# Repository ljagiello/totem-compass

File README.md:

# Totem Compass firmware — reverse engineering

Independent, unofficial reverse-engineering notes for the **Totem Compass** ESP32
firmware (**v5.0.3**; v5.0.2 was analyzed first, see
[What changed in 5.0.3](docs/firmware/changes-5.0.3.mdx)), produced by static analysis of the
publicly downloadable firmware images and the companion mobile app, plus a BLE client tested
against the author's own device. Not affiliated with or endorsed by Totem Labs.

## Key findings

- The device is an **ESP32** (Xtensa LX6) running **MicroPython v1.25.0** on **ESP-IDF v5.4**.
- Totem's application is **Python**, frozen into the image as bytecode across **94 frozen modules** in v5.0.3 (96 in v5.0.2), plus 2 non-frozen on-flash `.py` files.
- Three radios share the 2.4 GHz band: **BLE** (phone app), **ESP-NOW** ("Unity Mesh",
  Totem-to-Totem), and **WiFi** (station-mode OTA; the hotspot path is sunset).
- Application messages use a shared `(cat_id, cmd_id)` model with a common chunking layer.

## Documentation

Full docs live in [`docs/`](docs/) as a [Mintlify](https://mintlify.com) site.

```bash
cd docs
npm i -g mint    # or: npx mint@latest
mint dev         # preview at http://localhost:3000
```

Start at [`docs/index.mdx`](docs/index.mdx). The 2.4 GHz protocol capture — with a
completeness matrix — is under [`docs/protocols/`](docs/protocols/).

## Go client: `totemctl`

A Bluetooth LE client that speaks the same protocol as the official app: the
ConnStatus-Ready handshake, Live/Static/Peer records, and the half-duplex TX
handoff. No pairing or keys are needed.

```bash
go install github.com/ljagiello/totem-compass/cmd/totemctl@latest

totemctl scan                     # find Totems (double-press the power button first)
totemctl info                     # name, firmware, battery, position, settings
totemctl watch                    # stream live data and peer updates
totemctl peers                    # bonded Totems and points of interest
totemctl name "Base Camp"         # rename
totemctl compass --lock on --north off --blink on
totemctl power eco --blink on     # or: normal
totemctl wifi scan                # networks the Totem can see
totemctl wifi set <ssid>          # network used for firmware updates; asks for the password
totemctl peer color <mac> hot_pink
totemctl poi add --name "Main Stage" --lat 50.0671 --lon 19.9124 --sticky
totemctl location --lat 50.0671 --lon 19.9124  # feed a phone-style GNSS fix + clock
```

Pick a device with `-d <address substring>`, using an address `totemctl scan`
prints: every Totem advertises as "totem", so the name set with `totemctl name`
cannot select one. Get machine-readable output with `--json`, and log every
frame with `--trace`. `totemctl help <command>` lists each command's flags.

Every global flag can also be set as a `TOTEM_<FLAG>` environment variable
(`TOTEM_DEVICE`, `TOTEM_HALF_DUPLEX`, …) or in a config file with the long flag
names as keys (`device: <address from totemctl scan>`). The default location is
`totemctl/config.yaml` under the user config directory (`~/Library/Application
Support` on macOS, `~/.config` on Linux), or pass `--config`.

`compass` and `power` send a frame that always sets peer blink, which the Totem
does not report, so they need `--blink on|off`; set it once with `blink: on` in
the config file or `TOTEM_BLINK`.

The Ready frame's schema id selects one of two device transmit loops. The
client defaults to the legacy full-duplex loop (schema 0: notifications plus
app-level acks), which works on every platform. The newer half-duplex loop
(`--half-duplex`) sends indications and drops a record unless it is confirmed
within 500 ms; CoreBluetooth subscribes these characteristics for
notifications only, so that mode stalls on macOS.

Verified on hardware from macOS: `scan` and `info` on firmware 4.1.3 and 5.0.3; `watch` and
`compass --lock on|off` round-trips on 4.1.3. The other commands are built from the
v5.0.2/v5.0.3 bytecode (their handlers are identical in both) and covered by unit tests
only.

| Package | Contents |
| --- | --- |
| [`protocol/`](protocol/) | frame builders and decoders, no BLE dependency; tested against vectors built with the firmware's own `struct` formats |
| [`client/`](client/) | scanning, connecting, subscriptions, acks and TX-window handling on [`tinygo.org/x/bluetooth`](https://github.com/tinygo-org/bluetooth) (tested on macOS; the library also supports Linux/BlueZ and Windows) |
| [`cmd/totemctl/`](cmd/totemctl/) | the CLI |

## ESP32 emulator: `totememu`

An ESP32 running TinyGo that joins the ESP-NOW mesh as another Totem: it pairs with a real
Totem through the normal Touch Crystal pairing and then exchanges peer status with it every
radio window. It models the rest of the device too — the halo and the crystal, the Touch
Crystal and the two buttons, the power state and its battery curve, an update over WiFi —
and keeps its name, colour and bonds in flash across a power cut. Hardware-tested against
firmware 5.0.3. See [`docs/reference/esp32-emulator.mdx`](docs/reference/esp32-emulator.mdx).

```bash
tinygo flash -target esp32-generic -ldflags "-X main.owned=<your Totem's MAC>" ./cmd/totememu

totemctl mesh pair                # hold the Totem's Touch Crystal next to the board
totemctl mesh watch               # decode every frame the Totem sends it (--raw, --tx, --json)
totemctl mesh status              # the emulator and its peers
totemctl mesh clock               # give the board this computer's time
totemctl mesh send pos 50.0671 19.9124 3   # where it is
totemctl mesh send sim walk 90             # and where it goes: walk, drive or still
totemctl mesh send batt 40                 # also: sos, heading, flat, unbond, selftest
totemctl mesh send touch crystal hold 1500 # a gesture, as a finger would make it
totemctl mesh send leds                    # what the ring and the crystal are doing
```

The `mesh` commands find the board's USB serial port by itself (or take `--port`,
`TOTEM_PORT`, `port:` in the config file). They open it without toggling DTR/RTS, so the
board does not reboot, and they decode the raw frames on the host with the `mesh` package.

| Package | Contents |
| --- | --- |
| [`mesh/`](mesh/) | ESP-NOW frame codec (peer, locate, Smart Group), tested against frames packed with the firmware's own `struct` formats |
| [`emulator/`](emulator/) | the Totem logic: pairing, radio windows, clock sync, locate reply and relay, Smart Group member, the halo and crystal, the touch and button gestures, the power state and the WiFi update, and a model of the GNSS receiver, compass, motion sensor and battery; host-tested |
| [`store/`](store/) | the settings and bonds a reboot keeps, as an append-only journal in one flash sector |
| [`cmd/totememu/`](cmd/totememu/) | the ESP32 firmware and its serial console |

## Scope & ethics

The firmware analysis is static and no service was attacked; the releases API and firmware
objects are served publicly. The only code run against hardware is `totemctl`, over BLE, and
`totememu`, over ESP-NOW, both on the author's own Totem. See
[`docs/reference/methodology.mdx`](docs/reference/methodology.mdx). Use them only with devices
you own. The mesh and demi-god paths can affect other people's Totems nearby, so `totemctl`
does not send those commands, and `totememu` talks only to the Totems it is built for, never
hosts a Smart Group and never sends demi-god commands.

## License

Licensed under the [Apache License 2.0](LICENSE).

Created by [Lukasz Jagiello](https://lukasz.jagiello.org). Write-up: [lukasz.jagiello.org/projects/totem-compass](https://lukasz.jagiello.org/projects/totem-compass).

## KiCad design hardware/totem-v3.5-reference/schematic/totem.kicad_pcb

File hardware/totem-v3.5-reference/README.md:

# Totem v3.5 — reference design

A working circuit built from the parts identified on a Totem v3.5, with the
values chosen by calculation and checked in ngspice.

**This is a reconstruction, not a recovery.** The parts and the MCU pin
assignments are established — the parts off the board, the pins out of the
firmware, both cited in [the hardware page](../../docs/reference/hardware.mdx).
Everything else here is *designed to satisfy those facts*, not traced from the
PCB. Resistor values, the regulator topology, the LED supply arrangement: all
chosen here. Where a value is derived from something the firmware does, the
derivation is shown, and that is the strongest claim any of it makes.

Passive values cannot be recovered from photographs of an assembled board.
What can be done is to work out what they would have to be for the firmware to
behave as it does, and then check that circuit holds up. That is what this is.

## What the firmware pins down

Two constants in the firmware constrain the analog design tightly enough to
solve for it.

### The battery divider is determined, not chosen

The firmware converts its ADC reading with a fixed calibration
(`docs/subsystems/power.mdx`, `compass.dis:1446`):

```python
battery_volt = 0.0017 * self.v_supply.read() + 0.206
```

`ADC.read()` returns 0..4095. Writing the whole chain out, with `k` the
divider ratio, `VFS` the ATTN_11DB full scale and `Voff` the ADC's input
offset:

```
cal(V) = 0.0017 * 4095 * (k*V - Voff)/VFS + 0.206
```

For `cal(V) == V` at every V, both coefficients must match:

```
k    = VFS / (0.0017 * 4095) = 3.3 / 6.9615 = 0.4741
Voff = 0.206 * VFS / 6.9615  = 97.7 mV
```

The offset is not fitted — it falls out of the same two equations, and
**97.7 mV is the ESP32 ADC's well-known input offset**. That it lands there
is the evidence the model has the right shape, and it is why the `+0.206` in
the firmware is an ADC artefact rather than a fudge.

A resistor marked `124` — 120 kΩ — is on the board. Taking that as the top
leg, the ratio asks for 108.2 kΩ below it, and no standard series has that
(E96 goes 107, 110; E192 107, 109). An earlier version named a 108 kΩ
part, which is not made; the nearest that is, 109 kΩ, reads a full cell
17 mV high, over the 10 mV the checks allow. So this board uses
**113 kΩ over 102 kΩ**, both E96 and both made in 0.1%: k within 0.08% of
the firmware's, drawing 19.5 µA.
Simulated, the firmware's own calibration then reads the cell **true to
3.3 mV** across 3.4–4.2 V, against 68 mV for the 120k/100k pair tried first.

### GPIO 39 is a VBUS divider, not the charger's status pin

`modes.is_charging = self.v_in.value()` — high means charging. The TP4056's
`CHRG` is open-drain and pulls **low** while charging, and GPIO 34–39 have no
internal pull of any kind, so an open-drain source would float when idle.
Both facts are wrong for `CHRG` and right for a divider off VBUS, which also
matches the firmware's own name for it: `v_in`, the input voltage.

100 kΩ over 150 kΩ clears the logic threshold at a sagging 4.40 V charger and
stays under the absolute maximum at 5.25 V, with margin at both ends.

## Verification

```
cd sim && python3 check.py
```

Requires `ngspice` (`brew install ngspice`). Each deck computes; `check.py`
decides whether the number is allowed, and prints a line per claim. Current
state: **18 passed, 0 failed, 1 known limit recorded**.

| Block | Result |
| --- | --- |
| `batt_sense` | Pin at 1.993 V on a full cell, inside the ADC's 150–2450 mV window. Calibration true to 3.3 mV. Divider (113k over 102k) draws 19.5 µA |
| `vbus_sense` | 2.64 V at 4.40 V in (165 mV over V<sub>IH</sub>), 3.15 V at 5.25 V (450 mV under absolute max). 21 µA |
| `ldo_headroom` | Rail holds 3.293 V at a 3.4 V cell under a 532 mA peak — 293 mV over the ESP32's minimum. Fails only at 3.107 V, *below* the firmware's cutoff |
| `led_budget` | With the 1515's 15.5 mA per pixel: normal use is 0.15 C, all 67 pixels at full white at the firmware's brightness 0.62 C; 1 C would take 107. Known limit: the pixels want 3.5 V and the firmware runs the cell to 3.15 V |

The digital parts are modelled as current sinks at their datasheet peaks, and
the regulator and charger behaviourally, because no vendor models are to hand.
These verify the design's arithmetic, not anyone's silicon.

The whole board is simulated too, built from the schematic's own netlist
rather than from a hand-written deck:

```
cd sim && python3 board_sim.py
```

**78 passed, 0 failed, 1 known limit**, over five corners (cell at 4.2, 3.8
and 3.4 V; the 2N7002's threshold at 2.1 and 2.5 V). Each corner runs one
4.5-second sequence — off, press on, press while running, ring on and off,
firmware power-off, on again, held through a firmware power-off, released —
and checks the rail, GPIO 4's voltage limits and the cell's idle drain at each
step. Steady-state checks cover the rail at a TX peak with the ring lit across
the firmware's battery bands, every pixel at full white, both sense dividers
and charging. The known limit is the ring's supply at a 3.45 V cell, 3.34 V
against the 1515 LEDs' 3.5 V rating, which the reference board shares: its
ring hangs off the cell the same way.

## The board

`schematic/totem.kicad_pcb`, made by scripts in `pcb/` from the schematic
and from measurements of the reference board's photographs (`measure/`,
whose README says how, and how well, each number is known):

```
cd pcb
KP=/Applications/KiCad/KiCad.app/Contents/Frameworks/Python.framework/Versions/Current/bin/python3
$KP build.py      # outline, parts where the photos put them, nets, planes, rules
python route.py   # the router (numpy, scipy, opencv)
$KP apply.py      # tracks and vias into the board, zones filled
$KP models.py     # 3D models for the parts KiCad's library has none for
python3 fab.py    # everything for the fab and the assembler -> pcb/fab/
```

**To have boards made, hand over `pcb/fab/totem-v3.5-assembly-package.zip`.** It
holds gerbers and drills (and ODB++ and IPC-2581), the BOM and placement file,
assembly drawings, the schematic, a STEP model, and
[`pcb/ASSEMBLY.md`](pcb/ASSEMBLY.md): what to order, how to assemble, bring up
and program the board, and what to measure before ordering.

Four layers, 1.6 mm: signals on both outer layers, In1 solid GND, In2 3V3.
Tracks 0.13 mm and 0.13 mm apart, power nets 0.4 mm with 0.2 mm; vias
0.45/0.2 mm; copper 0.3 mm from the edge — a mainstream 4-layer process with
margin. The GNSS antenna feed is a straight, via-free 0.38 mm microstrip on
F.Cu over In1: 50 Ω on a standard 1.6 mm 4-layer stack-up (about 0.21 mm of
7628 prepreg under the top layer); order that stack-up, or re-size the line
for another. The LED side's ring is powered through a VLED pour outside the
ring, fed at C16 and, past the one place the ring's data has to cross it,
at D159.

Both sides carry parts (the LED side: ring, crystal, motion sensor and
magnetometer, microphone, the charge LEDs, the power latch), so assembly is
double-sided. The placement file is KiCad's;
assembly houses differ in how they read rotations on the bottom side, so
check their preview of the LED side — the ring's orientation rule is that
each LED's DI and VDD pads face out.

**`kicad-cli pcb drc --schematic-parity --severity-all`: 0 violations,
0 unconnected pads, 0 footprint errors.** Three places where the reference
board is closer than KiCad's courtyard and silkscreen margins allow (the
TP4056 0.3 mm from the module, the SOS LED between its switch's legs) are
narrow rules in `schematic/totem.kicad_dru`, each with its reason. The
router (`pcb/route.py`) also checks every net's connectivity itself before
it hands over.

What is the reference board's and what is not:

| | |
| --- | --- |
| Outline, notches, the tab | Measured: ±0.3 mm on the left half and bottom, **±1.3 mm in height on the right side** (the two photos disagree there) |
| ESP32, MAX-M10S, TP4056, LDO, u.FL, P-FET, switches, SOS LED | Measured from their pads |
| The ring | Measured: centre (−2.02, 2.45), radius 18.24 mm, 60 LEDs every 6°, **1.5 mm packages** |
| The crystal, its pogo-pin post, the IMU's site, the microphone | Measured |
| The two charge LEDs and their two resistors in the crystal, the JST's pins | Measured from close-ups of the LED side |
| The motion sensor and magnetometer | This design's: the reference board's ICM-20948 is obsolete, so an ST LSM6DSV16X sits on its site with an LIS2MDL beside it (below) |
| Passives, the latch, the ring's driver | This design's, placed beside what they serve |
| About 25 small parts in the reference board's LED-side cluster below the crystal, and a column of about 8 between the ring and the crystal | Photographed, not copied: their values and nets run under the parts and on inner layers. This design's own circuit does the jobs they must do (latch, ring switch, decoupling) |
| Every trace | Routed here; the original's are not recoverable |

**Measure these on the reference board before ordering** — each is where a
photograph could not settle it:

- **The board's height at the right edge**, and the distance from the USB-C
  to the lower-right notch: the right side is known to ±1.3 mm.
- **The USB-C.** The original's is a through-hole-shell part: on the LED
  side its four plated slots sit 4.80 mm either side of the centre line in
  two rows 3.0 mm apart, with two round holes 6.5 mm apart (measured,
  `measure/`). No catalogue footprint checked matches that (HRO
  TYPE-C-31-M-12, GCT USB4105 and USB4125, SHOU HAN TYPE-C 6P and its
  recessed 6P). The one used here, a power-only GCT USB4135, is the library
  part that clears the ring behind it; its plug face ends up **about 0.6 mm
  or more further in** than the original's (1.75 mm overhang). Check it
  against the case, and measure the original's if it can be taken out.
- **The JST** is the through-hole S2B-PH-K-S on the reference board's own
  pin positions (their solder joints, 1.96 mm apart, show on the LED side);
  its housing overhangs the lower-right chamfer as the original's does.
  Check the cable's exit against the case.
- **Button stem height.** The switches are 6 x 6 mm top-actuated tact
  switches with tall stems that go through the rear cover; the BOM names a
  9.5 mm one. The stem has to be matched to the cover.
- **The touch pogo pin**: a gold spring-loaded pin standing on the 2.5 mm
  pad at the centre of the crystal (close-up photo). Measure its length,
  barrel and travel on the reference unit: its length sets the pressure on
  the crystal.

Two things are derived, not seen:

- **Where the ring starts and which way it counts.** The links between the
  ring's LEDs run on an inner layer on the reference board, so its chain can
  not be followed. The firmware maps a bearing to pixel
  `(60 − bearing // 6) mod 60`, counter-clockwise-positive under its
  Madgwick convention, with pixel 0 along the IMU's +X; the IMU's marking puts
  +X toward the buttons. So D100 is the LED nearest the buttons and the chain
  runs counter-clockwise seen from the LED side. If the compass shows
  mirrored or rotated on the first board, this is where to look.
- **The sensors' axes.** U5 (LSM6DSV16X) and U6 (LIS2MDL) sit square to the
  board and to each other, each with pin 1 at its upper-left seen from the
  radio side (`pcb/build.py`). Their axes in the board's frame follow from
  that, from ST's axis drawings (DS13510 Figure 5, DS12144 Figure 2) and from
  their being on the LED side, which mirrors them. Confirm on the first
  board before trusting a heading: lay it flat and see which axis reads 1 g,
  then turn it and see which magnetometer axis follows north.

### Parts changed from the reference board

The board is built from parts in production. Each was checked on DigiKey or
LCSC on 2026-09-30; these are the ones that changed:

| Reference board / earlier version | Here | Why |
| --- | --- | --- |
| TDK ICM-20948 (U5) | ST **LSM6DSV16X** (U5) + **LIS2MDL** (U6), both on I2C0, interrupts to IO32 and IO33 | DigiKey: obsolete, "no longer manufactured". The ST pair is current and its sensors are better on every figure both datasheets give (table below) |
| CUI CMC-4013-SMT-TR microphone | Same Sky **CMC-4013-2-SMT-TR** | Obsolete; the -2 has the same 4 mm can and -42 dB, and its pads fall inside this footprint's |
| Everlight 19-217 red LED (SOS) | Lite-On **LTST-C191KRKT** | Not available; the green of the same series is discontinued |
| Charger status outputs left open (earlier version) | Two 0603 LEDs, red and green (D4, D5), with 1k each | The reference board has two 0603 LEDs in the crystal below the touch post; colours not visible unlit |
| SMD JST S2B-PH-SM4-TB (earlier version) | THT **S2B-PH-K-S** | The reference board's is through-hole (above) |
| "PTS645SH95SMTR92 LFS" (earlier version) | **PTS645SK95SMTR92 LFS** | The earlier part number does not exist; SK95 is the 9.5 mm SMT variant in stock |
| 108k cell-sense resistor (earlier version) | **109k** | No 108k is made (above) |

The motion sensors, from the three datasheets (TDK DS-000189 Rev 1.6;
ST DS13510 Rev 4, DS12144 Rev 6), typical values:

| | ICM-20948 | LSM6DSV16X + LIS2MDL |
| --- | --- | --- |
| Gyro noise density | 0.015 dps/√Hz | 0.0028 dps/√Hz |
| Gyro zero-rate drift over temperature | ±0.05 dps/°C | ±0.006 dps/°C |
| Accelerometer noise density | 230 µg/√Hz | 60 µg/√Hz |
| Accelerometer offset drift over temperature | ±0.80 mg/°C | ±0.07 mg/°C |
| Magnetometer initial offset | ±300 µT | ±6 µT |
| Magnetometer noise | not specified | 0.3 µT RMS |

The LIS2MDL's datasheet asks for currents above 10 mA to be kept "a few
millimeters away" (section 5.2): it sits 4.8 mm inside the ring's LEDs and
13 mm from the latch, and the router keeps every power net's track and via
3.5 mm from its centre (`MAG_KEEPOUT` in `pcb/route.py`). The charger, 5.4 mm
away on the radio side, carries its current only while charging.

## The schematic, and its ERC

```
cd schematic && python3 totem.py
```

Requires `skidl` (`pip3 install --user skidl`). The circuit is described as
code rather than drawn, which makes the connectivity machine-checkable:
SKiDL's ERC looks for pins left floating and for nets with two things driving
them. It writes `totem.net`, a KiCad netlist, and `totem.erc`.

**Current state: 0 ERC errors and 0 ERC warnings.**

An earlier version left the TP4056's `CHRG` and `STDBY` status outputs open
and ERC reported both. They now drive the two charge LEDs the reference
board has in its crystal, so nothing is left open on purpose.

Netlist generation separately reports 27 `No footprint for …` errors. Those
are not design faults — no footprints are assigned because this is a
schematic-level design with no board layout intended.

Getting there took four real corrections, which is the argument for running it
at all rather than drawing a diagram and trusting it:

- Three `POWER-OUT` conflicts, where I had the TP4056's two `BAT` pins and the
  cell all declared as independent drivers of `VBAT`. Pins 5 and 6 are one
  node on the die, and the cell shares that node rather than fighting it.
- A fourth on `GND`, from declaring connector grounds as drivers.
- `TEMP` left floating. The TP4056 needs it tied off when no thermistor is
  fitted, which is easy to forget and silent when forgotten.
- The regulator's `EN` left floating — which is where the GPIO 4 power gate
  has to live, so the warning was pointing at a missing part of the design.

A fifth was mine rather than the design's, and is worth recording because of
how it hid. Trying to silence the two status-pin warnings, I imported a name
SKiDL 2.3.0 does not export. The script then died on the import — but the
run before it had been `rm -f totem.erc` followed by the script with output
sent to `/dev/null`, so an empty file was left behind and read back as a
clean result. **An absent report is not a passing one.** `check.py` fails
loudly on a missing measurement for the same reason; this checker now
insists the ERC file exists before believing it.

### Real symbols, and what that bought

Parts come from **KiCad's own symbol libraries** wherever they exist —
ESP32-WROOM-32E, MAX-M10S, ICM-20948, WS2812B, and the passives — so the
netlist carries real package pin numbers rather than labels invented here.
Only the TP4056 is still declared inline, because KiCad has no symbol for it.

This is not cosmetic. On the module, pins 4 and 5 are named `SENSOR_VP` and
`SENSOR_VN` — GPIO 36 and GPIO 39, the microphone and the VBUS sense.
Wiring against the real symbol is what puts those on the correct physical
pins. Two things the real symbols caught that a hand-written pin list could
not:

- **`EN` was unconnected.** The ESP32 will not run with its enable floating,
  and it needs the pull-up and capacitor that give it a power-on reset. The
  hazard of a pin list written by hand is that a pin nobody thought of is
  also a pin nobody notices is missing.
- **`RESV` is typed NO-CONNECT** on the ICM-20948 symbol, and I had tied it
  to ground. The symbol is authored from the datasheet, so it wins.

### The sheet

```
python3 gen_sch.py                                    # writes totem.kicad_sch
kicad-cli sch erc --output totem_erc.rpt totem.kicad_sch
kicad-cli sch export svg --output . totem.kicad_sch   # writes totem.svg
```

**Open `totem.kicad_sch` in KiCad.** It is generated from the same `totem.py`
the ERC checks, so the drawing cannot drift away from the netlist, and it
embeds KiCad's own symbol definitions — the drawing of a resistor is KiCad's
drawing of a resistor.

It is drawn the way a schematic is drawn. **Rails carry KiCad's power
symbols** at each pin, which is how every real sheet does it and which took
about 150 labels off the drawing. **Short point-to-point runs are wired**, so
a divider or an RC is a line you can follow. **Signals with several
destinations keep a label**, which is also what a real sheet does.

A first version put a label on every pin instead. It passed ERC and was
unreadable — nothing on it *looked* connected, which fails the only job a
schematic has.

Long routes are deliberately not drawn, and ERC is the reason. Routing every
two-ended net with an automatic corner produced this:

```
[multiple_net_names]: Both ESP_EN and POWER_EN are attached to the same items
```

A wire endpoint had landed on another net's wire and shorted two separate
nets together — a drawing that looked right and was electrically wrong. Runs
longer than 45 mm are labelled rather than routed for that reason. Laying
those out properly is hand work in KiCad, on top of this file.

**KiCad's own ERC: 0 errors, 2 warnings.** Both are explainable and left
reported. `SDO/AD0` is the ICM-20948's address-select pin strapped low, which
KiCad notes because a bidirectional pin is sitting on a power net. `PROG` is
isolated because U3 is not on the sheet at all — the TP4056 has no KiCad
symbol, so it is the one part that cannot be drawn, and `gen_sch.py` says so
when it runs rather than quietly omitting it.

Getting there took three rounds, each of which is a thing a hand-drawn sheet
would have hidden:

- **124 off-grid endpoints**, from a 40 mm margin that is not a multiple of
  KiCad's 1.27 mm grid. With a label on every pin, one careless constant is
  one violation per pin.
- **35 unconnected pins**, now carrying explicit no-connect markers, which is
  how a schematic says "deliberately" rather than leaving a reader to guess.
- **A symbol that drew as nothing.** `AP2127K-3.3` *extends* `AP2204K-1.5`,
  so its own block holds properties and no pins at all. Embedded as it comes,
  the regulator would have landed on the sheet with no pins to attach a wire
  to. `kicad_sexp.py` flattens inherited symbols for that reason.

### The earlier drawing, and why it went

SKiDL 2.3.0 cannot draw this circuit: both `generate_svg` and
`generate_schematic` crash in its `kicad10` backend on the real multi-unit
symbols (`gen_svg.py:310`, `AttributeError: 'NoneType' object has no
attribute 'net'`). That is why `gen_sch.py` exists and writes the sheet
directly.

An earlier SVG did exist, made when the parts were simplified inline
definitions, and it was **deleted rather than kept**: once the parts became
real symbols it no longer matched the netlist, and a picture that disagrees
with the netlist is worse than no picture.

## Three findings worth keeping

**The firmware protects the hardware, not the other way round.** The 3V3 rail
only collapses below the ESP32's 3.0 V minimum at a cell voltage of 3.107 V.
The firmware gives up on the cell around 3.4 V, so it always stops first —
about 290 mV of margin.

**Every pixel at full white is 2.41 A, or 2.41 C.** A 1000 mAh pouch cell is
good for about 1 C, so the ring simply cannot be filled white at the default
brightness; the ceiling is 27.8 pixels. This is not a flaw in the design, it
is a constraint the firmware already respects — it lights north and the peers,
and eco mode blanks the ring entirely. It does mean any future animation that
fills the ring has a current budget to answer to.

**The pixels are under-supplied at the bottom of the discharge.** WS2812B want
VDD ≥ 3.5 V and the firmware runs the cell to 3.4 V, leaving them 100 mV
short. The strips cannot move to the 3V3 rail instead — that is further below
their minimum, and 2.4 A through a linear regulator is not a circuit anyone
builds. Either the fitted pixels are a low-voltage variant, or colour accuracy
degrades near empty. Both are testable on the bench; neither is settled here.

A fourth is a caution rather than a finding: 481 mW in the pass element at a
full cell would be 120 °C of rise in a SOT-23-5 at θ<sub>JA</sub> ≈ 250 °C/W.
That figure is the **peak**, at a 500 mA radio transmit burst with a
low duty cycle, so it is transient and the average is far below it. A design
that drew that continuously would need a different package or a switcher.

## Not covered

- **The reference board's traces and inner layers.** Not recoverable from an
  assembled board; this board is routed afresh (see "The board").
- **The GNSS UART pins** on the module side are taken from the firmware's
  `UART(1, rx=16, tx=17)`, not traced.
- **The `J22B` SOT-23-5 and the `A7` / `65KS` SOD-123s** on the LED side.
  Legible markings, nets untraced. The `A7` is the usual marking of a
  1N4148W, which this design's latch uses; the rest are left out rather than
  drawn in wrongly. (What was listed here as a separate "U6" SOIC-14 marked
  `I2948` is the IMU itself, photographed at an angle.)
- **The power gate's topology** is designed to the firmware's behaviour, not
  recovered: GPIO 4 read as an input while running, re-opened as an output and
  driven low to switch off. It is simulated in every corner above.

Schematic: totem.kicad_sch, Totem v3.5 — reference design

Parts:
C1, C4, C6, C7, C12, C19, C21: 100n; C_0603_1608Metric
C2, C18: 1u; C_0603_1608Metric
C3, C5, C10, C11, C13, C14, C15, C16, C17, C20: 10u; C_0805_2012Metric
C8: 220n; C_0603_1608Metric
D1: 1N4148W; D_SOD-123
D2: BAT54W; SOT-323_SC-70
D3, D4: red; LED_0603_1608Metric
D5: green; LED_0603_1608Metric
D100, D101, D102, D103, D104, D105, D106, D107, D108, D109, D110, D111, D112, D113, D114, D115, D116, D117, D118, D119, D120, D121, D122, D123, D124, D125, D126, D127, D128, D129, D130, D131, D132, D133, D134, D135, D136, D137, D138, D139, D140, D141, D142, D143, D144, D145, D146, D147, D148, D149, D150, D151, D152, D153, D154, D155, D156, D157, D158, D159, D200, D201, D202, D203, D204, D205, D206: XL-1515RGBC-WS2812B; LED_XL-1515RGBC-WS2812B
J1: USB4135-GF-A; USB_C_Receptacle_GCT_USB4135-GF-A_6P_TopMnt_Horizontal
J2: LiPo 1000mAh; JST_PH_S2B-PH-K_1x02_P2.00mm_Horizontal
J3: u.FL; U.FL_Hirose_U.FL-R-SMT-1_Vertical
MK1: electret; CUI_CMC-4013-SMT_RingGap
Q1, Q4: AO3401A; SOT-23
Q2, Q3, Q5: 2N7002; SOT-23
R1: 113k; R_0603_1608Metric
R2: 102k; R_0603_1608Metric
R3, R9, R10, R14, R18, R24, R25: 100k; R_0603_1608Metric
R4: 150k; R_0603_1608Metric
R5: 2k; R_0603_1608Metric
R6: 330; R_0603_1608Metric
R7, R8: 4.7k; R_0603_1608Metric
R11, R12: 33; R_0603_1608Metric
R13, R17, R19, R22, R26: 10k; R_0603_1608Metric
R15: 10M; R_0603_1608Metric
R16: 1M; R_0603_1608Metric
R20, R21: 5.1k; R_0603_1608Metric
R23: 2.2k; R_0603_1608Metric
R27, R28: 1k; R_0603_1608Metric
SW1: power; SW_SPST_PTS645Sx43SMTR92
SW2: SOS; SW_SPST_PTS645Sx43SMTR92
TP1: touch pogo pin; TestPoint_Pad_D2.5mm
TP2: 3V3; TestPoint_Pad_D1.0mm
TP3: GND; TestPoint_Pad_D1.0mm
TP4: TXD0; TestPoint_Pad_D1.0mm
TP5: RXD0; TestPoint_Pad_D1.0mm
TP6: EN; TestPoint_Pad_D1.0mm
TP7: IO0; TestPoint_Pad_D1.0mm
U1: ESP32-WROOM-32E
U2: MAX-M10S; ublox_MAX
U3: TP4056-42-ESOP8; SOIC-8-1EP_3.9x4.9mm_P1.27mm_EP2.29x3mm
U4: AP2112K-3.3; SOT-23-5
U5: LSM6DSV16X; LGA-14_3x2.5mm_P0.5mm_LayoutBorder3x4y
U6: LIS2MDL; LGA-12_2x2mm_P0.5mm

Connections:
+3V3: C1.1, C3.1, C4.1, C5.1, C6.1, C7.1, C14.1, C19.1, C20.1, C21.1, R7.1, R8.1, R13.1, R16.1, R19.1, R22.1, R23.1, R24.1, TP2.1, U1.2 (VDD), U2.6 (V_BCKP), U2.7 (VCC_IO), U2.8 (VCC), U4.5 (VOUT), U5.5 (VDDIO), U5.8 (VDD), U5.12 (CS), U6.3 (~CS), U6.9 (Vdd), U6.10 (Vdd_IO)
/BTN: D1.2 (A), Q3.1 (G), R18.1, SW1.2
/BTN_SOS: R22.2, SW2.1, TP7.1, U1.25 (IO0)
/CC1: J1.A5 (CC1), R20.1
/CC2: J1.B5 (CC2), R21.1
/CHRG: D4.1 (K), U3.7 (~CHRG)
/CRYSTAL_DATA: R12.1, U1.33 (IO21)
/CRY_D0: D200.3 (DIN), R12.2
/ESP_EN: C2.1, R13.2, TP6.1, U1.3 (EN)
/GATE_MAIN: Q1.1 (G), Q2.3 (D), R14.2
/GNSS_RF: J3.1 (In), U2.11 (RF_IN)
/GNSS_RX: U1.28 (IO17), U2.3 (RXD)
/GNSS_TX: U1.27 (IO16), U2.2 (TXD)
/GPIO4: D2.3 (K), Q3.3 (D), R19.2, U1.26 (IO4)
/HOLD: C12.1, D1.1 (K), Q2.1 (G), R15.1, R16.2, R17.1
/I2C0_SCL: R8.2, U1.11 (IO26), U5.13 (SCL), U6.1 (SCL/SPC)
/I2C0_SDA: R7.2, U1.10 (IO25), U5.14 (SDA), U6.4 (SDA/SDI/SDO)
/IMU_INT1: U1.8 (IO32), U5.4 (INT1)
/IMU_SA0: R26.1, U5.1 (SDO/SA0), U5.2 (SDX), U5.3 (SCX)
/LED_EN: Q5.1 (G), R10.1, U1.31 (IO19)
/MAG_C1: C8.1, U6.5 (C1)
/MAG_DRDY: U1.9 (IO33), U6.7 (DRDY)
/MIC: C18.2, R24.2, R25.1, U1.4 (SENSOR_VP)
/MIC_RAW: C18.1, MK1.2 (+), R23.2
/PROG: R5.1, U3.2 (PROG)
/RING_D0: D100.3 (DIN), R11.2
/RING_D20: D119.1 (DOUT), D120.3 (DIN)
/RING_D40: D139.1 (DOUT), D140.3 (DIN)
/RING_DATA: R11.1, U1.30 (IO18)
/RING_GATE: Q4.1 (G), Q5.3 (D), R9.2
/RXD0: TP5.1, U1.34 (RXD0/IO3)
/SOS_LED: R6.1, U1.13 (IO14)
/SOS_LED_A: D3.2 (A), R6.2
/STDBY: D5.1 (K), U3.6 (~STDBY)
/TOUCH: TP1.1, U1.12 (IO27)
/TXD0: TP4.1, U1.35 (TXD0/IO1)
/VBAT_SENSE: R1.2, R2.1, U1.6 (IO34)
/VBUS_SENSE: R3.2, R4.1, U1.5 (SENSOR_VN)
GND: C1.2, C2.2, C3.2, C4.2, C5.2, C6.2, C7.2, C8.2, C10.2, C11.2, C12.2, C13.2, C14.2, C15.2, C16.2, C17.2, C19.2, C20.2, C21.2, D3.1 (K), D100.2 (VSS), D101.2 (VSS), D102.2 (VSS), D103.2 (VSS), D104.2 (VSS), D105.2 (VSS), D106.2 (VSS), D107.2 (VSS), D108.2 (VSS), D109.2 (VSS), D110.2 (VSS), D111.2 (VSS), D112.2 (VSS), D113.2 (VSS), D114.2 (VSS), D115.2 (VSS), D116.2 (VSS), D117.2 (VSS), D118.2 (VSS), D119.2 (VSS), D120.2 (VSS), D121.2 (VSS), D122.2 (VSS), D123.2 (VSS), D124.2 (VSS), D125.2 (VSS), D126.2 (VSS), D127.2 (VSS), D128.2 (VSS), D129.2 (VSS), D130.2 (VSS), D131.2 (VSS), D132.2 (VSS), D133.2 (VSS), D134.2 (VSS), D135.2 (VSS), D136.2 (VSS), D137.2 (VSS), D138.2 (VSS), D139.2 (VSS), D140.2 (VSS), D141.2 (VSS), D142.2 (VSS), D143.2 (VSS), D144.2 (VSS), D145.2 (VSS), D146.2 (VSS), D147.2 (VSS), D148.2 (VSS), D149.2 (VSS), D150.2 (VSS), D151.2 (VSS), D152.2 (VSS), D153.2 (VSS), D154.2 (VSS), D155.2 (VSS), D156.2 (VSS), D157.2 (VSS), D158.2 (VSS), D159.2 (VSS), D200.2 (VSS), D201.2 (VSS), D202.2 (VSS), D203.2 (VSS), D204.2 (VSS), D205.2 (VSS), D206.2 (VSS), J1.A12 (GND), J1.B12 (GND), J1.SH (SHIELD), J2.2, J3.2 (Ext), MK1.1 (-), Q2.2 (S), Q3.2 (S), Q5.2 (S), R2.2, R4.2, R5.2, R10.2, R15.2, R18.2, R20.2, R21.2, R25.2, R26.2, SW2.2, TP3.1, U1.1, U1.15, U1.38, U1.39, U1.[1,15,38,39] (GND), U2.1 (GND), U2.10 (GND), U2.12 (GND), U3.1 (TEMP), U3.3 (GND), U3.9 (EPAD), U4.2 (GND), U5.6 (GND), U5.7 (GND), U6.6 (GND), U6.8 (GND)
unnamed: D2.1 (A), R17.2
unnamed: D4.2 (A), R27.2
unnamed: D5.2 (A), R28.2
unnamed: D100.1 (DOUT), D101.3 (DIN)
unnamed: D101.1 (DOUT), D102.3 (DIN)
unnamed: D102.1 (DOUT), D103.3 (DIN)
unnamed: D103.1 (DOUT), D104.3 (DIN)
unnamed: D104.1 (DOUT), D105.3 (DIN)
unnamed: D105.1 (DOUT), D106.3 (DIN)
unnamed: D106.1 (DOUT), D107.3 (DIN)
unnamed: D107.1 (DOUT), D108.3 (DIN)
unnamed: D108.1 (DOUT), D109.3 (DIN)
unnamed: D109.1 (DOUT), D110.3 (DIN)
unnamed: D110.1 (DOUT), D111.3 (DIN)
unnamed: D111.1 (DOUT), D112.3 (DIN)
unnamed: D112.1 (DOUT), D113.3 (DIN)
unnamed: D113.1 (DOUT), D114.3 (DIN)
unnamed: D114.1 (DOUT), D115.3 (DIN)
unnamed: D115.1 (DOUT), D116.3 (DIN)
unnamed: D116.1 (DOUT), D117.3 (DIN)
unnamed: D117.1 (DOUT), D118.3 (DIN)
unnamed: D118.1 (DOUT), D119.3 (DIN)
unnamed: D120.1 (DOUT), D121.3 (DIN)
unnamed: D121.1 (DOUT), D122.3 (DIN)
unnamed: D122.1 (DOUT), D123.3 (DIN)
unnamed: D123.1 (DOUT), D124.3 (DIN)
unnamed: D124.1 (DOUT), D125.3 (DIN)
unnamed: D125.1 (DOUT), D126.3 (DIN)
unnamed: D126.1 (DOUT), D127.3 (DIN)
unnamed: D127.1 (DOUT), D128.3 (DIN)
unnamed: D128.1 (DOUT), D129.3 (DIN)
unnamed: D129.1 (DOUT), D130.3 (DIN)
unnamed: D130.1 (DOUT), D131.3 (DIN)
unnamed: D131.1 (DOUT), D132.3 (DIN)
unnamed: D132.1 (DOUT), D133.3 (DIN)
unnamed: D133.1 (DOUT), D134.3 (DIN)
unnamed: D134.1 (DOUT), D135.3 (DIN)
unnamed: D135.1 (DOUT), D136.3 (DIN)
unnamed: D136.1 (DOUT), D137.3 (DIN)
unnamed: D137.1 (DOUT), D138.3 (DIN)
unnamed: D138.1 (DOUT), D139.3 (DIN)
unnamed: D140.1 (DOUT), D141.3 (DIN)
unnamed: D141.1 (DOUT), D142.3 (DIN)
unnamed: D142.1 (DOUT), D143.3 (DIN)
unnamed: D143.1 (DOUT), D144.3 (DIN)
unnamed: D144.1 (DOUT), D145.3 (DIN)
unnamed: D145.1 (DOUT), D146.3 (DIN)
unnamed: D146.1 (DOUT), D147.3 (DIN)
unnamed: D147.1 (DOUT), D148.3 (DIN)
unnamed: D148.1 (DOUT), D149.3 (DIN)
unnamed: D149.1 (DOUT), D150.3 (DIN)
unnamed: D150.1 (DOUT), D151.3 (DIN)
unnamed: D151.1 (DOUT), D152.3 (DIN)
unnamed: D152.1 (DOUT), D153.3 (DIN)
unnamed: D153.1 (DOUT), D154.3 (DIN)
unnamed: D154.1 (DOUT), D155.3 (DIN)
unnamed: D155.1 (DOUT), D156.3 (DIN)
unnamed: D156.1 (DOUT), D157.3 (DIN)
unnamed: D157.1 (DOUT), D158.3 (DIN)
unnamed: D158.1 (DOUT), D159.3 (DIN)
unnamed: D200.1 (DOUT), D201.3 (DIN)
unnamed: D201.1 (DOUT), D202.3 (DIN)
unnamed: D202.1 (DOUT), D203.3 (DIN)
unnamed: D203.1 (DOUT), D204.3 (DIN)
unnamed: D204.1 (DOUT), D205.3 (DIN)
unnamed: D205.1 (DOUT), D206.3 (DIN)
VBAT: C11.1, J2.1, Q1.2 (S), R14.1, SW1.1, U3.5 (BAT)
VBUS: C10.1, J1.A9 (VBUS), J1.B9 (VBUS), R3.1, R27.1, R28.1, U3.4 (V_{CC}), U3.8 (CE)
VLED: C15.1, C16.1, D100.4 (VDD), D101.4 (VDD), D102.4 (VDD), D103.4 (VDD), D104.4 (VDD), D105.4 (VDD), D106.4 (VDD), D107.4 (VDD), D108.4 (VDD), D109.4 (VDD), D110.4 (VDD), D111.4 (VDD), D112.4 (VDD), D113.4 (VDD), D114.4 (VDD), D115.4 (VDD), D116.4 (VDD), D117.4 (VDD), D118.4 (VDD), D119.4 (VDD), D120.4 (VDD), D121.4 (VDD), D122.4 (VDD), D123.4 (VDD), D124.4 (VDD), D125.4 (VDD), D126.4 (VDD), D127.4 (VDD), D128.4 (VDD), D129.4 (VDD), D130.4 (VDD), D131.4 (VDD), D132.4 (VDD), D133.4 (VDD), D134.4 (VDD), D135.4 (VDD), D136.4 (VDD), D137.4 (VDD), D138.4 (VDD), D139.4 (VDD), D140.4 (VDD), D141.4 (VDD), D142.4 (VDD), D143.4 (VDD), D144.4 (VDD), D145.4 (VDD), D146.4 (VDD), D147.4 (VDD), D148.4 (VDD), D149.4 (VDD), D150.4 (VDD), D151.4 (VDD), D152.4 (VDD), D153.4 (VDD), D154.4 (VDD), D155.4 (VDD), D156.4 (VDD), D157.4 (VDD), D158.4 (VDD), D159.4 (VDD), Q4.3 (D)
VSYS: C13.1, C17.1, D200.4 (VDD), D201.4 (VDD), D202.4 (VDD), D203.4 (VDD), D204.4 (VDD), D205.4 (VDD), D206.4 (VDD), Q1.3 (D), Q4.2 (S), R1.1, R9.1, U4.1 (VIN), U4.3 (EN)

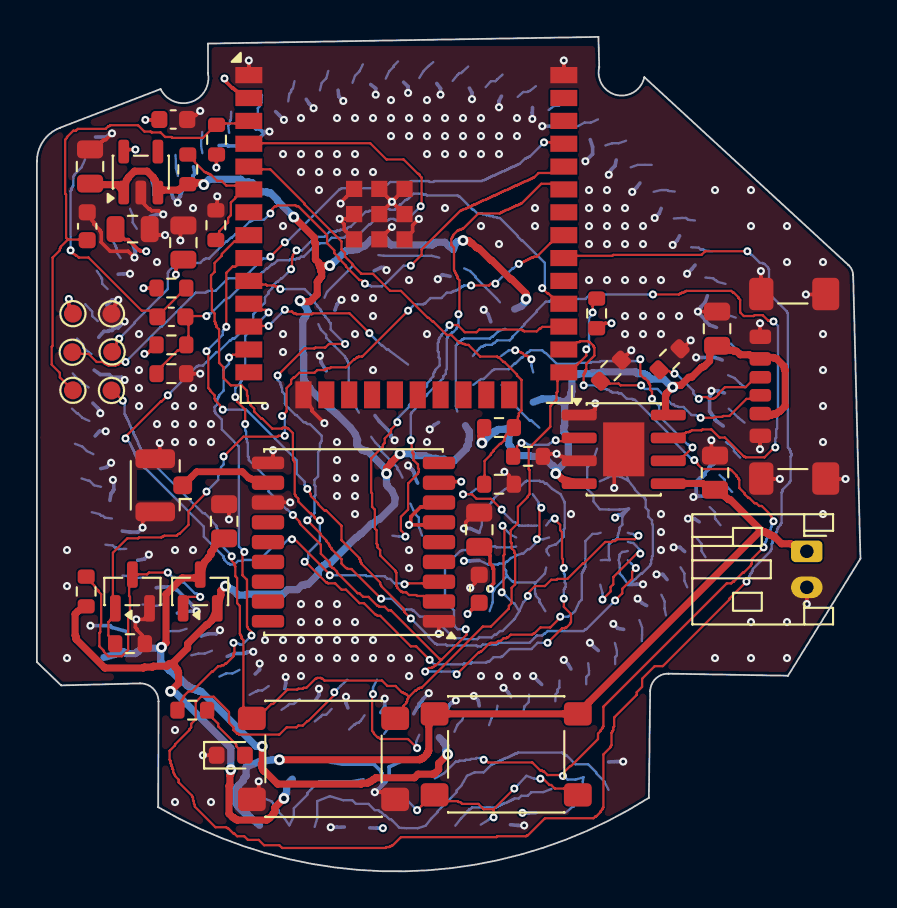
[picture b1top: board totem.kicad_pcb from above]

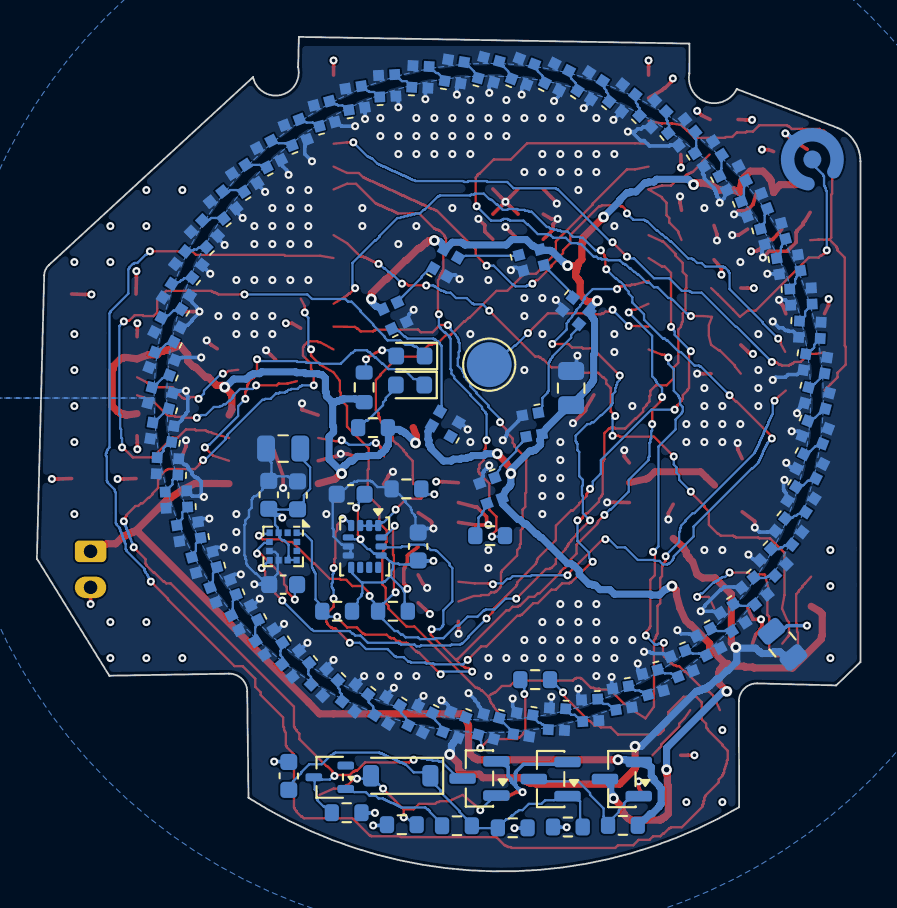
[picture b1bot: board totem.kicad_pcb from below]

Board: 4 copper layers, 45.8 x 46.4 mm, 144 parts (100 on the bottom side), 109 nets.

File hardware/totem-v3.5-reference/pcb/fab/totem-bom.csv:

Comment,Designator,Footprint,Quantity,Side,Manufacturer,MPN,Note
100n,"C1,C7,C12,C19,C21",C_0603_1608Metric,5,Bottom,Samsung,CL10B104KB8NNNC,0603 X7R 50 V
220n,C8,C_0603_1608Metric,1,Bottom,Samsung,CL10B224KB8NNNC,"0603 X7R 50 V, low ESR: the LIS2MDL's set/reset capacitor"
10u,"C16,C17,C20",C_0805_2012Metric,3,Bottom,Samsung,CL21A106KAYNNNE,0805 X5R 25 V
1N4148W,D1,D_SOD-123,1,Bottom,Diodes Inc.,1N4148W-7-F,
BAT54W,D2,SOT-323_SC-70,1,Bottom,Diodes Inc.,BAT54W-7-F,
red,D4,LED_0603_1608Metric,1,Bottom,Lite-On,LTST-C191KRKT,0603 red
green,D5,LED_0603_1608Metric,1,Bottom,Lite-On,LTST-C191KGKT,0603 green
XL-1515RGBC-WS2812B,"D100,D101,D102,D103,D104,D105,D106,D107,D108,D109,D110,D111,D112,D113,D114,D115,D116,D117,D118,D119,D120,D121,D122,D123,D124,D125,D126,D127,D128,D129,D130,D131,D132,D133,D134,D135,D136,D137,D138,D139,D140,D141,D142,D143,D144,D145,D146,D147,D148,D149,D150,D151,D152,D153,D154,D155,D156,D157,D158,D159,D200,D201,D202,D203,D204,D205,D206",LED_XL-1515RGBC-WS2812B,67,Bottom,XINGLIGHT,XL-1515RGBC-WS2812B,"1.5 x 1.5 mm addressable RGB; moisture sensitive, bake per datasheet"
electret,MK1,CUI_CMC-4013-SMT_RingGap,1,Bottom,Same Sky (CUI Devices),CMC-4013-2-SMT-TR,
AO3401A,Q1,SOT-23,1,Bottom,Alpha & Omega,AO3401A,
2N7002,"Q2,Q3",SOT-23,2,Bottom,Nexperia,"2N7002,215",
4.7k,"R7,R8",R_0603_1608Metric,2,Bottom,Yageo,RC0603FR-074K7L,0603 1% 100 mW
33,"R11,R12",R_0603_1608Metric,2,Bottom,Yageo,RC0603FR-0733RL,0603 1% 100 mW
100k,"R14,R18",R_0603_1608Metric,2,Bottom,Yageo,RC0603FR-07100KL,0603 1% 100 mW
10M,R15,R_0603_1608Metric,1,Bottom,Yageo,RC0603FR-0710ML,0603 1% 100 mW
1M,R16,R_0603_1608Metric,1,Bottom,Yageo,RC0603FR-071ML,0603 1% 100 mW
10k,"R17,R19,R26",R_0603_1608Metric,3,Bottom,Yageo,RC0603FR-0710KL,0603 1% 100 mW
1k,"R27,R28",R_0603_1608Metric,2,Bottom,Yageo,RC0603FR-071KL,0603 1% 100 mW
touch pogo pin,TP1,TestPoint_Pad_D2.5mm,1,Bottom,-,-,"SMT spring-loaded (pogo) pin on a 2.5 mm pad, length to suit the crystal; hand-fitted, see ASSEMBLY.md"
LSM6DSV16X,U5,LGA-14_3x2.5mm_P0.5mm_LayoutBorder3x4y,1,Bottom,STMicroelectronics,LSM6DSV16XTR,"6-axis IMU, LGA-14L; moisture sensitive"
LIS2MDL,U6,LGA-12_2x2mm_P0.5mm,1,Bottom,STMicroelectronics,LIS2MDLTR,"3-axis magnetometer, LGA-12; keep it clear of magnetised tools and parts"
1u,"C2,C18",C_0603_1608Metric,2,Top,Samsung,CL10A105KB8NNNC,0603 X5R 50 V
10u,"C3,C5,C10,C11,C13,C14,C15",C_0805_2012Metric,7,Top,Samsung,CL21A106KAYNNNE,0805 X5R 25 V
100n,"C4,C6",C_0603_1608Metric,2,Top,Samsung,CL10B104KB8NNNC,0603 X7R 50 V
red,D3,LED_0603_1608Metric,1,Top,Lite-On,LTST-C191KRKT,0603 red
USB4135-GF-A,J1,USB_C_Receptacle_GCT_USB4135-GF-A_6P_TopMnt_Horizontal,1,Top,GCT,USB4135-GF-A,"power-only USB-C, 6 pin"
LiPo 1000mAh,J2,JST_PH_S2B-PH-K_1x02_P2.00mm_Horizontal,1,Top,JST,S2B-PH-K-S(LF)(SN),"battery connector, THT side entry; the cell is off-board (totem-offboard.csv)"
u.FL,J3,U.FL_Hirose_U.FL-R-SMT-1_Vertical,1,Top,Hirose,U.FL-R-SMT-1(10),GNSS antenna connector
AO3401A,Q4,SOT-23,1,Top,Alpha & Omega,AO3401A,
2N7002,Q5,SOT-23,1,Top,Nexperia,"2N7002,215",
113k,R1,R_0603_1608Metric,1,Top,Yageo,RT0603BRD07113KL,0603 0.1% thin film: cell-sense divider
102k,R2,R_0603_1608Metric,1,Top,Yageo,RT0603BRD07102KL,0603 0.1% thin film: cell-sense divider
100k,"R3,R9,R10,R24,R25",R_0603_1608Metric,5,Top,Yageo,RC0603FR-07100KL,0603 1% 100 mW
150k,R4,R_0603_1608Metric,1,Top,Yageo,RC0603FR-07150KL,0603 1% 100 mW
2k,R5,R_0603_1608Metric,1,Top,Yageo,RC0603FR-072KL,0603 1% 100 mW
330,R6,R_0603_1608Metric,1,Top,Yageo,RC0603FR-07330RL,0603 1% 100 mW
10k,"R13,R22",R_0603_1608Metric,2,Top,Yageo,RC0603FR-0710KL,0603 1% 100 mW
5.1k,"R20,R21",R_0603_1608Metric,2,Top,Yageo,RC0603FR-075K1L,0603 1% 100 mW
2.2k,R23,R_0603_1608Metric,1,Top,Yageo,RC0603FR-072K2L,0603 1% 100 mW
power,SW1,SW_SPST_PTS645Sx43SMTR92,1,Top,C&K,PTS645SK95SMTR92 LFS,"6x6 SMD tact, 9.5 mm; stem length to be matched to the rear cover"
SOS,SW2,SW_SPST_PTS645Sx43SMTR92,1,Top,C&K,PTS645SK95SMTR92 LFS,"6x6 SMD tact, 9.5 mm; stem length to be matched to the rear cover"
ESP32-WROOM-32E,U1,ESP32-WROOM-32E,1,Top,Espressif,ESP32-WROOM-32E-N4,"4 MB flash, as the firmware image"
MAX-M10S,U2,ublox_MAX,1,Top,u-blox,MAX-M10S-00B,"moisture sensitive, bake per u-blox before reflow"
TP4056-42-ESOP8,U3,SOIC-8-1EP_3.9x4.9mm_P1.27mm_EP2.29x3mm,1,Top,NanJing Top Power,TP4056-42-ESOP8,
AP2112K-3.3,U4,SOT-23-5,1,Top,Diodes Inc.,AP2112K-3.3TRG1,
